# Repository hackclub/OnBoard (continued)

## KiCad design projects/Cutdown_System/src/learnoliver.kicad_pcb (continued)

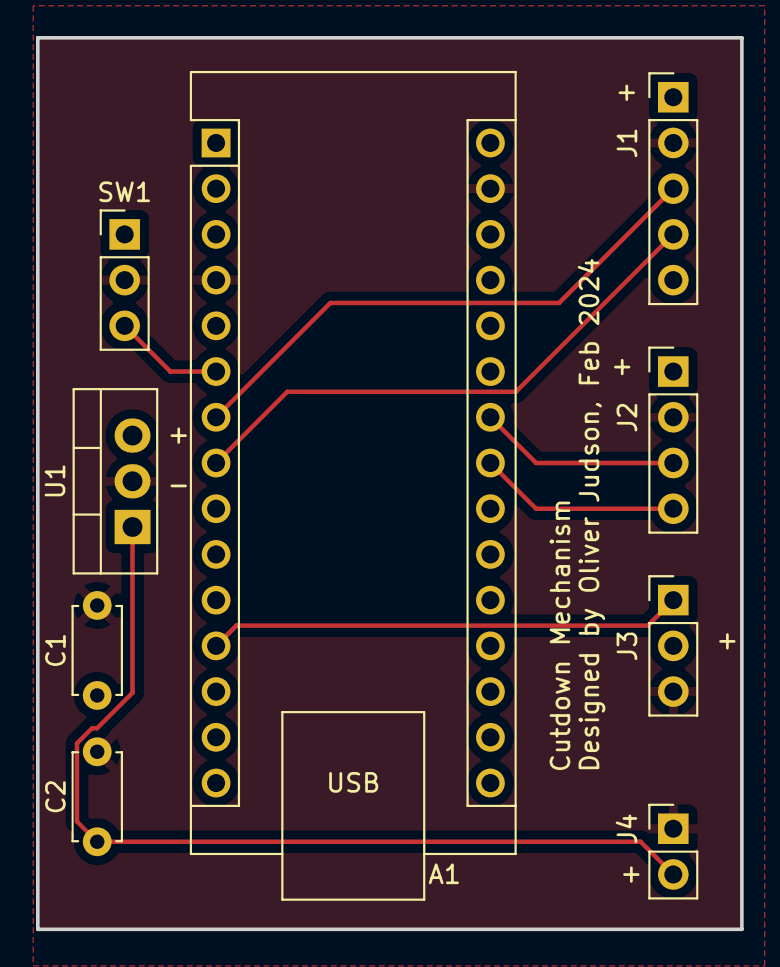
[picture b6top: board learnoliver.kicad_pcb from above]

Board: 2 copper layers, 39.1 x 49.5 mm, 9 parts (0 on the bottom side), 9 nets.

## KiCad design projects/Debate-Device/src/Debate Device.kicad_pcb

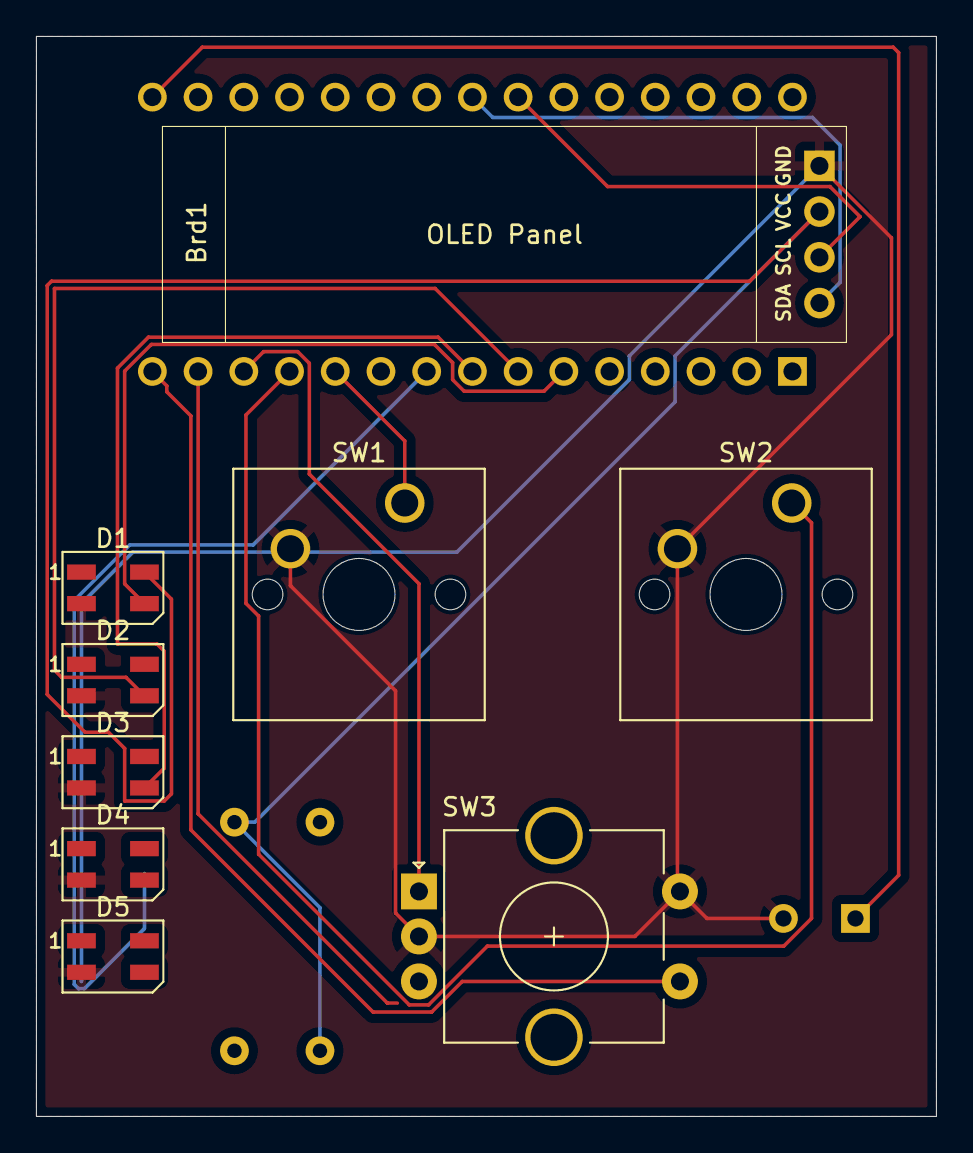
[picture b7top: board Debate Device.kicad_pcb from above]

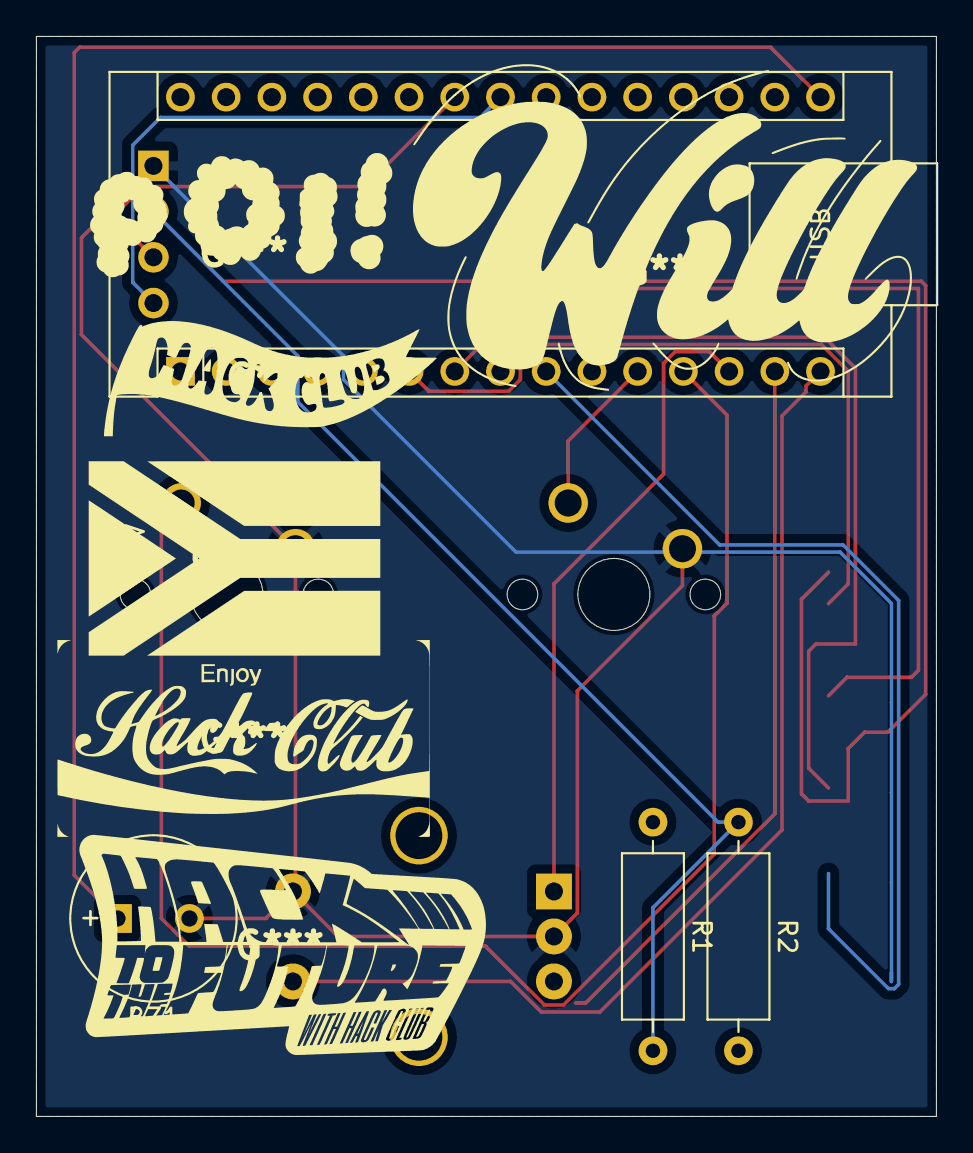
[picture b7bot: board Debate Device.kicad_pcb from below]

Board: 2 copper layers, 50.0 x 60.0 mm, 13 parts (4 on the bottom side), 15 nets.

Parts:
A1: Arduino_Nano_v3.x; Arduino_Nano
BZ1: Buzzer; MagneticBuzzer_PUI_AT-0927-TT-6-R
Brd1: SSD1306; SSD1306-0.91-OLED-4pin-128x32
D1, D2, D3, D4, D5: SK6812MINI; LED_SK6812MINI_PLCC4_3.5x3.5mm_P1.75mm
R1, R2: R; R_Axial_DIN0309_L9.0mm_D3.2mm_P12.70mm_Horizontal
SW1, SW2: SW_Push_LED; SW_Cherry_MX_1.00u_PCB
SW3: RotaryEncoder_Switch; RotaryEncoder_Alps_EC11E-Switch_Vertical_H20mm_CircularMoun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

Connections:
+5V: Brd1.2 (VCC), D1.4 (VDD), D2.4 (VDD), D3.4 (VDD), D4.4 (VDD), D5.4 (VDD), R1.2, R2.1
GND: BZ1.2 (-), Brd1.1 (GND), D1.2 (VSS), D2.2 (VSS), D3.2 (VSS), D4.2 (VSS), D5.2 (VSS), SW1.2, SW2.2, SW3.C, SW3.S2
unnamed: A1.23 (A4), Brd1.4 (SDA)
unnamed: A1.24 (A5), Brd1.3 (SCL)
unnamed: A1.6 (D3), D1.3 (DIN)
unnamed: A1.7 (D4), D2.3 (DIN)
unnamed: A1.8 (D5), D3.3 (DIN)
unnamed: A1.9 (D6), D4.3 (DIN)
unnamed: A1.10 (D7), D5.3 (DIN)
unnamed: A1.11 (D8), SW1.1
unnamed: A1.12 (D9), SW2.1
unnamed: A1.13 (D10), SW3.A
unnamed: A1.14 (D11), SW3.B
unnamed: A1.15 (D12), SW3.S1
unnamed: A1.16 (D13), BZ1.1 (+)
